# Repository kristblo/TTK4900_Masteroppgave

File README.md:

# TTK4900 Masteroppgave

Welcome to the Git repo of the master thesis project of Kristian Blom the spring of 2024, in which a defunct robotic arm from the 1990s was refurbished with new control hardware and software.

The main branch presents the project as it was at the end of the project's implementation, and shall not be altered until final censure has fallen on the project report.

The censure branch presents a curated version of project items deemed relevant to censure. Should the censor(s) find the main branch unnecessarily cluttered, this branch may be of interest.

### Directory: PCBs
Contains KiCad PCB design files.

### Directory: code/ros
Contains all code pertaining to ROS nodes and their configuration.

### Directory: code/stm config official
Contains all code pertaining to arm onboard software modules.

### Directory: documentation external
Contains hardware datasheets, application notes etc. for units used in the project. Most of these are cited as sources in the report.

### Directory: documentation internal
Contains documentation generated for the project.

The file journal.md contains notes taken during development.

A PDF version of the generated code documentation may be found here, in the file "kristian\_blom\_ttk4900\_documentation.pdf".

An HTML version of the generated code documentation may be found here, in the file "kristian\_blom\_ttk4900\_documentation\_html.zip". Its contents may be accessed by downloading and extracting the zip, then accessing "index.html" from a web browser.

Should the configuration of the STM32F303 processor be of interest, beyond what is presented in the thesis, an automatically generated report may be found in "stm\_config\_official.pdf"

Other items in this directory deemed relevant to the censure of the project are presented in the thesis, and may safely be ignored.

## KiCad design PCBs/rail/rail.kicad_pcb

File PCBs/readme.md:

###Folder purpose: PCB designs with Mk1.1 updates implemented, as well as production files such as gerbers

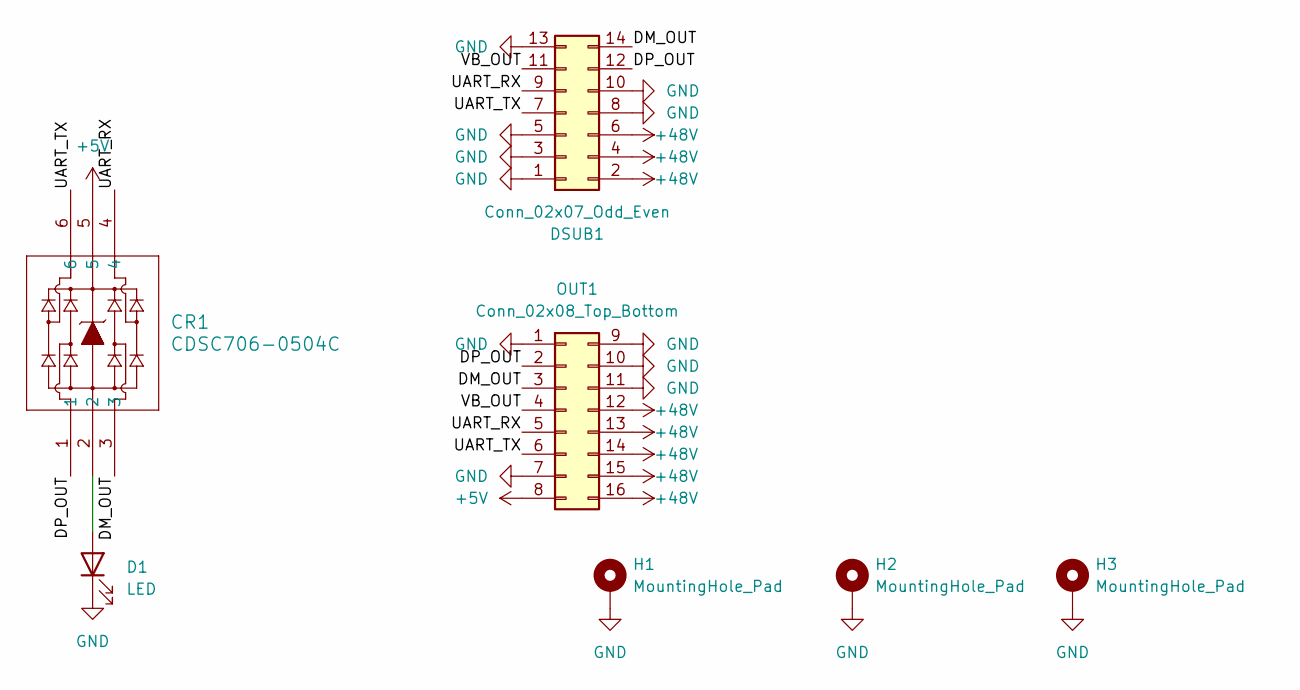
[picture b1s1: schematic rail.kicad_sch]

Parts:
CR1: CDSC706-0504C; CDSC706-0504C_BRN
D1: LED; LED_0603_1608Metric
DSUB1: Conn_02x07_Odd_Even; PinHeader_2x07_P2.54mm_Vertical
H1, H2, H3: MountingHole_Pad; MountingHole_3.2mm_M3_DIN965_Pad_TopBottom
OUT1: Conn_02x08_Top_Bottom; 2-1761603-6_TYC

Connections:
+5V: CR1.5, OUT1.8
+48V: DSUB1.2, DSUB1.4, DSUB1.6, OUT1.12, OUT1.13, OUT1.14, OUT1.15, OUT1.16
/DM_OUT: CR1.3, DSUB1.14, OUT1.3
/DP_OUT: CR1.1, DSUB1.12, OUT1.2
/UART_RX: CR1.4, DSUB1.9, OUT1.5
/UART_TX: CR1.6, DSUB1.7, OUT1.6
/VB_OUT: DSUB1.11, OUT1.4
GND: D1.1 (K), DSUB1.1, DSUB1.3, DSUB1.5, DSUB1.8, DSUB1.10, DSUB1.13, H1.1, H2.1, H3.1, OUT1.1, OUT1.7, OUT1.9, OUT1.10, OUT1.11
unnamed: CR1.2, D1.2 (A)

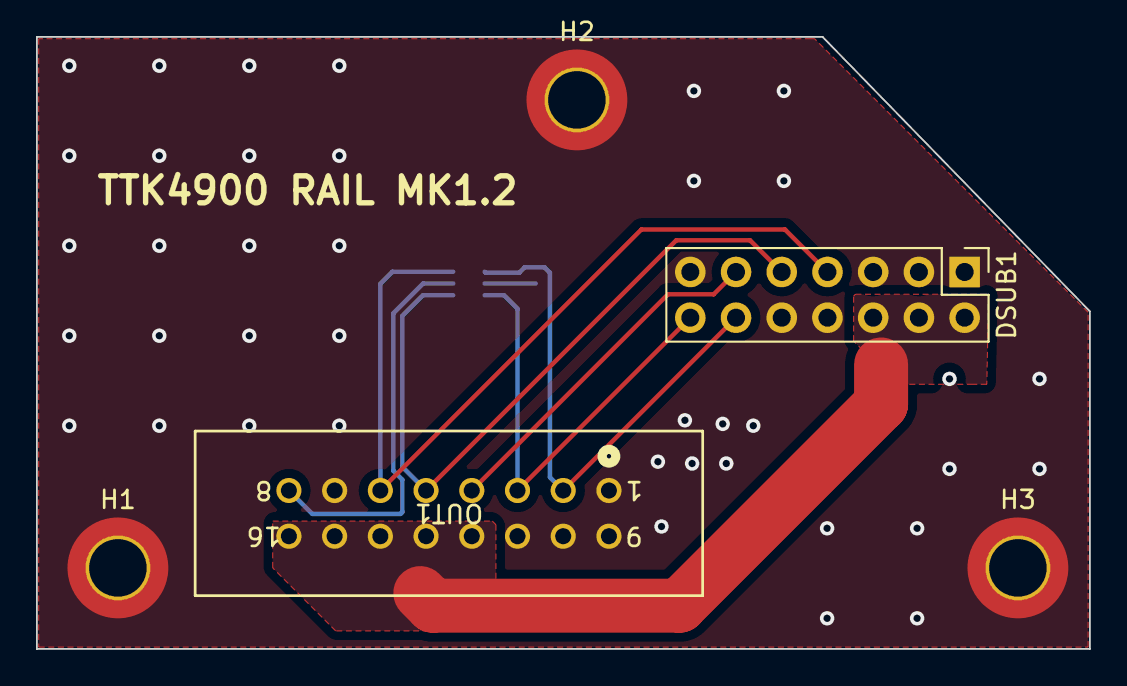
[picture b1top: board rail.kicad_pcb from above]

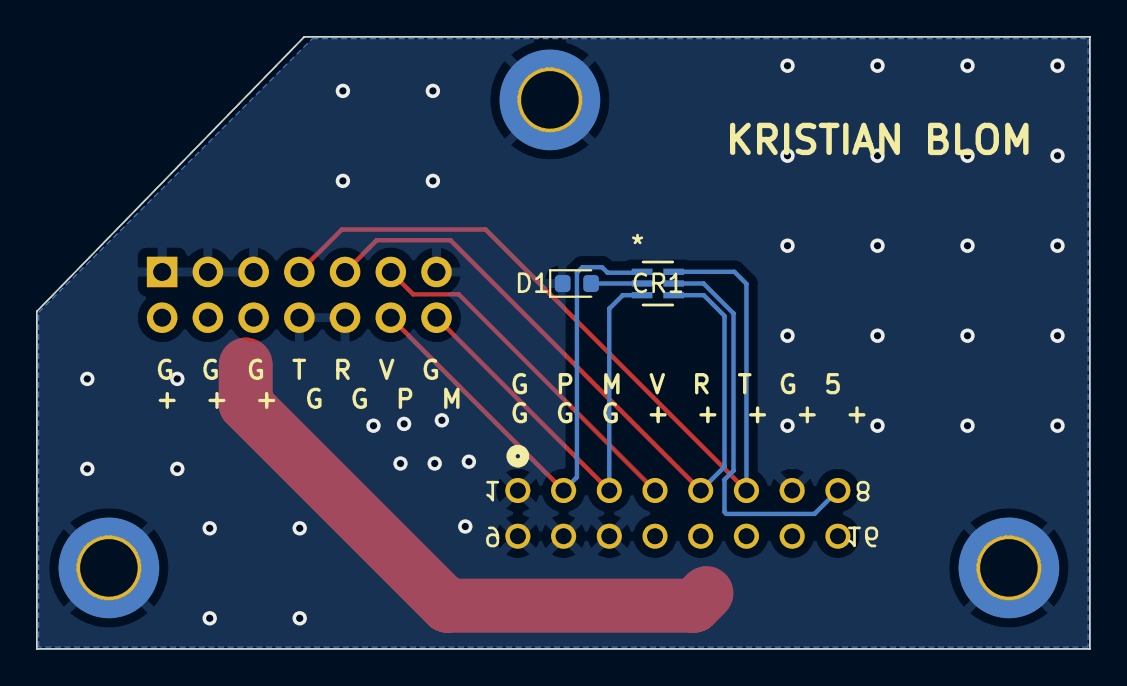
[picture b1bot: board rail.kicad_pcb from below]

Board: 2 copper layers, 58.5 x 34.0 mm, 7 parts (2 on the bottom side), 9 nets.

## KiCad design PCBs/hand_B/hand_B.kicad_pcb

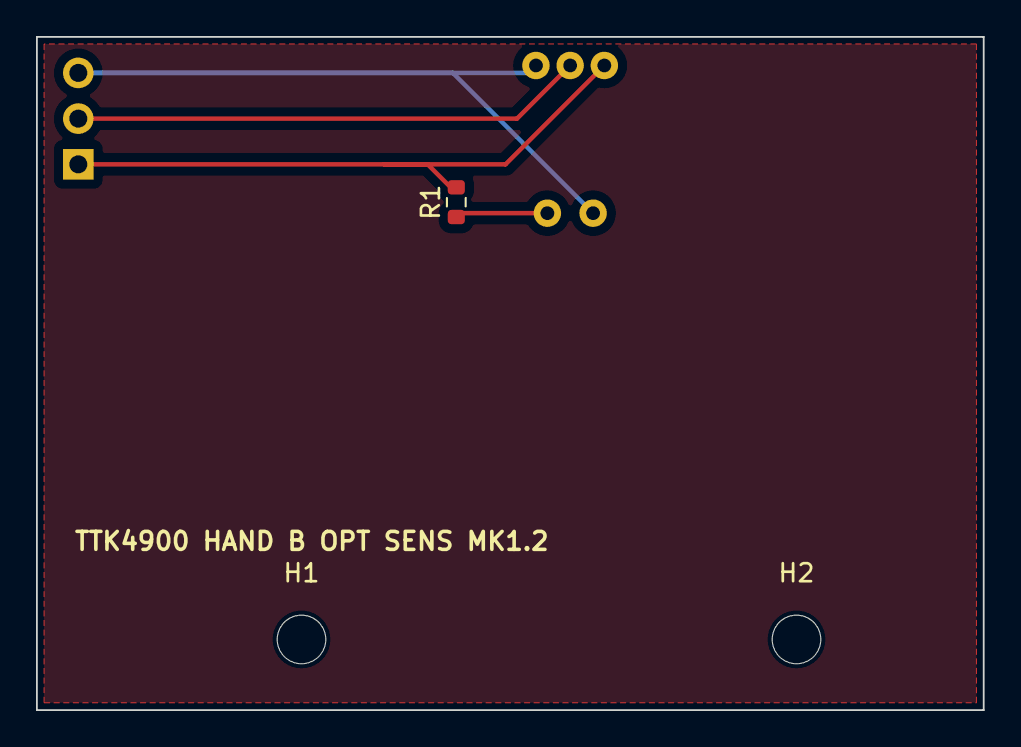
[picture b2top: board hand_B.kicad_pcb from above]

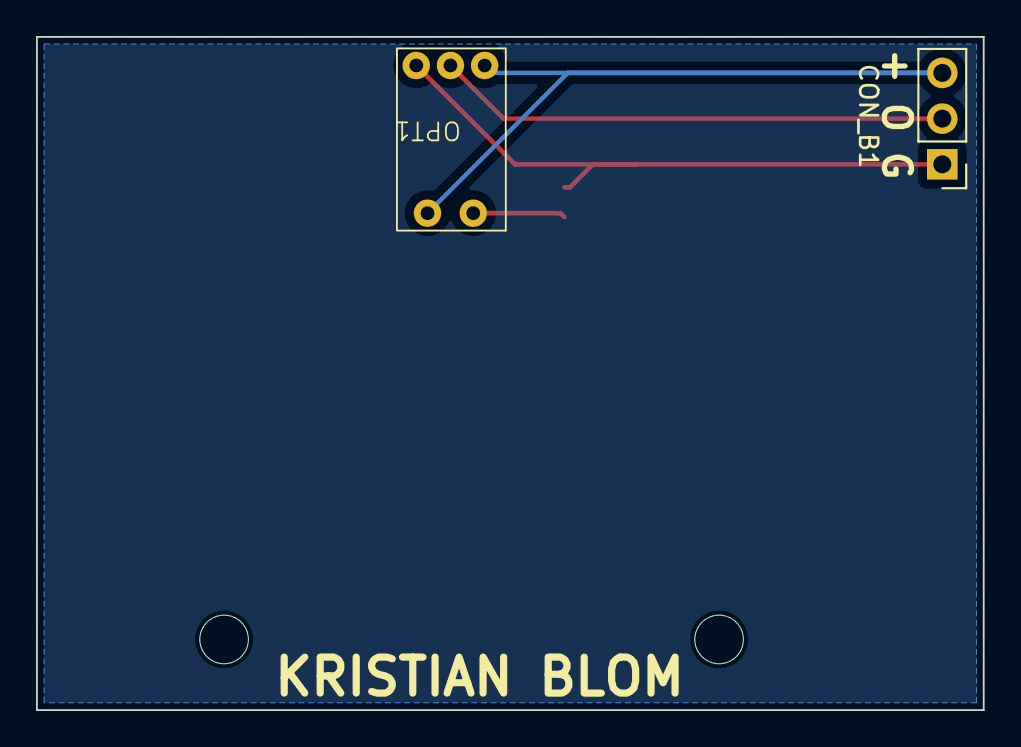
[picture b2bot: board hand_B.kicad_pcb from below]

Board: 2 copper layers, 52.6 x 37.4 mm, 5 parts (2 on the bottom side), 4 nets.

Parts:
CON_B1: Conn_01x03; PinHeader_1x03_P2.54mm_Vertical
H1, H2: MountingHole; MountingHole_2.7mm_M2.5
OPT1: OPB971N51
R1: 220; R_0603_1608Metric

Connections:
/0v: CON_B1.1, OPT1.5 (GND), R1.2
/5V: CON_B1.3, OPT1.1 (Anode), OPT1.3 (Vcc)
/OPT_B: CON_B1.2, OPT1.4 (Output)
unnamed: OPT1.2 (Cathode), R1.1

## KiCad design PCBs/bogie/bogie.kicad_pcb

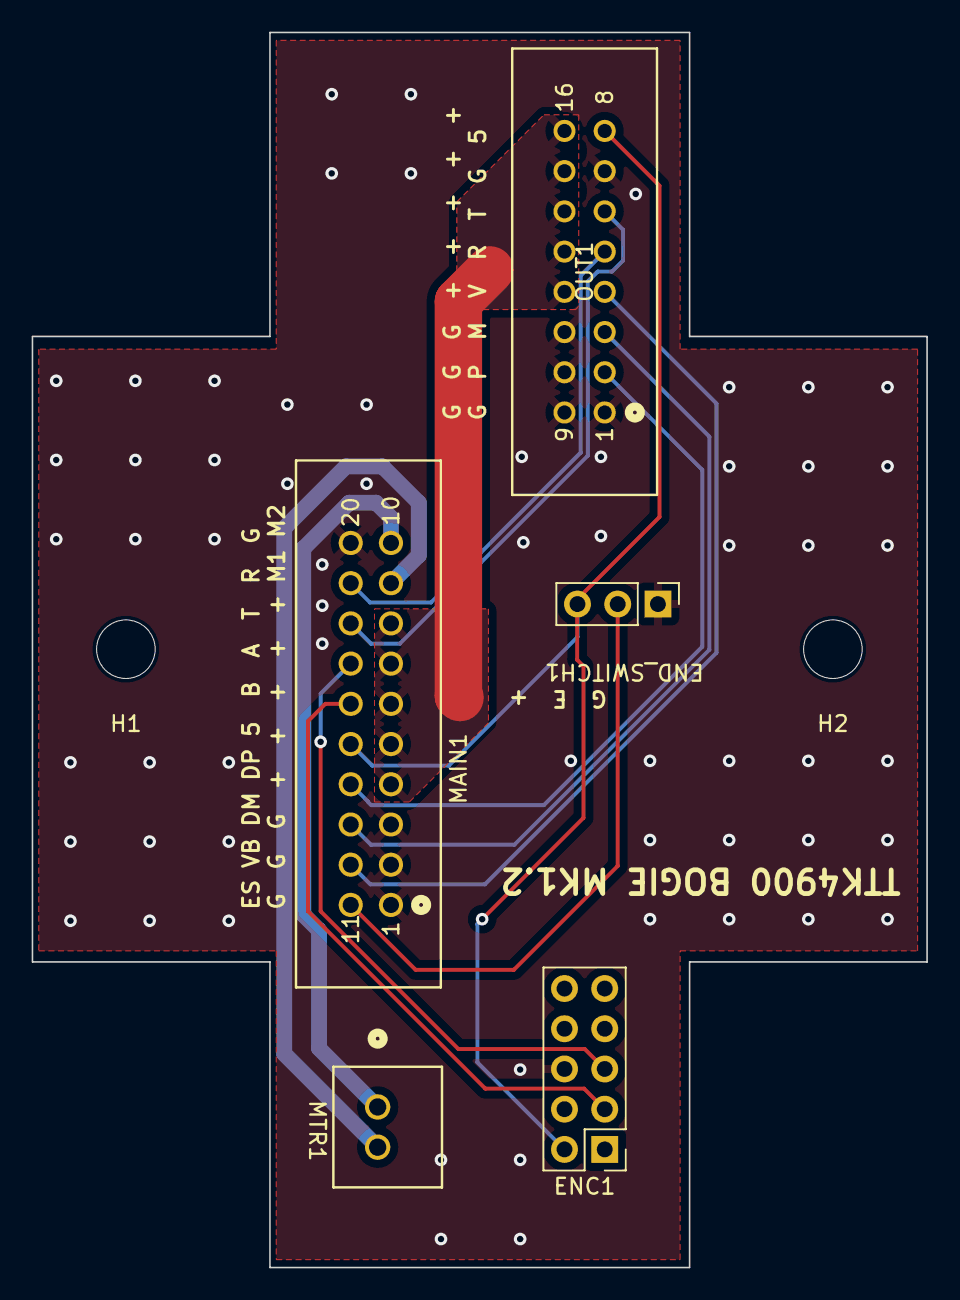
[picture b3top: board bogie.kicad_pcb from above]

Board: 2 copper layers, 56.5 x 78.0 mm, 7 parts (0 on the bottom side), 13 nets.

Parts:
ENC1: Conn_02x05_Odd_Even; PinHeader_2x05_P2.54mm_Vertical
END_SWITCH1: Conn_01x03; PinHeader_1x03_P2.54mm_Vertical
H1, H2: MountingHole; MountingHole_3.7mm
MAIN1: Conn_02x10_Top_Bottom; 1761681-7_TYC
MTR1: Conn_01x02; 70543-0001_MOL
OUT1: Conn_02x08_Top_Bottom; 2-1761603-6_TYC

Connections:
+5V: ENC1.2, END_SWITCH1.3, MAIN1.15, OUT1.8
+48V: MAIN1.4, MAIN1.5, MAIN1.6, MAIN1.7, MAIN1.8, OUT1.12, OUT1.13, OUT1.14, OUT1.15, OUT1.16
/DM_OUT: MAIN1.13, OUT1.3
/DP_OUT: MAIN1.14, OUT1.2
/ENC1A: ENC1.3, MAIN1.16
/ENC1B: ENC1.5, MAIN1.17
/END_SWITCH: END_SWITCH1.2, MAIN1.11
/MTR1_IN: MAIN1.10, MTR1.1
/MTR1_OUT: MAIN1.9, MTR1.2
/UART_RX: MAIN1.19, OUT1.5
/UART_TX: MAIN1.18, OUT1.6
/VB_OUT: MAIN1.12, OUT1.4
GND: ENC1.6, END_SWITCH1.1, MAIN1.1, MAIN1.2, MAIN1.3, MAIN1.20, OUT1.1, OUT1.7, OUT1.9, OUT1.10, OUT1.11

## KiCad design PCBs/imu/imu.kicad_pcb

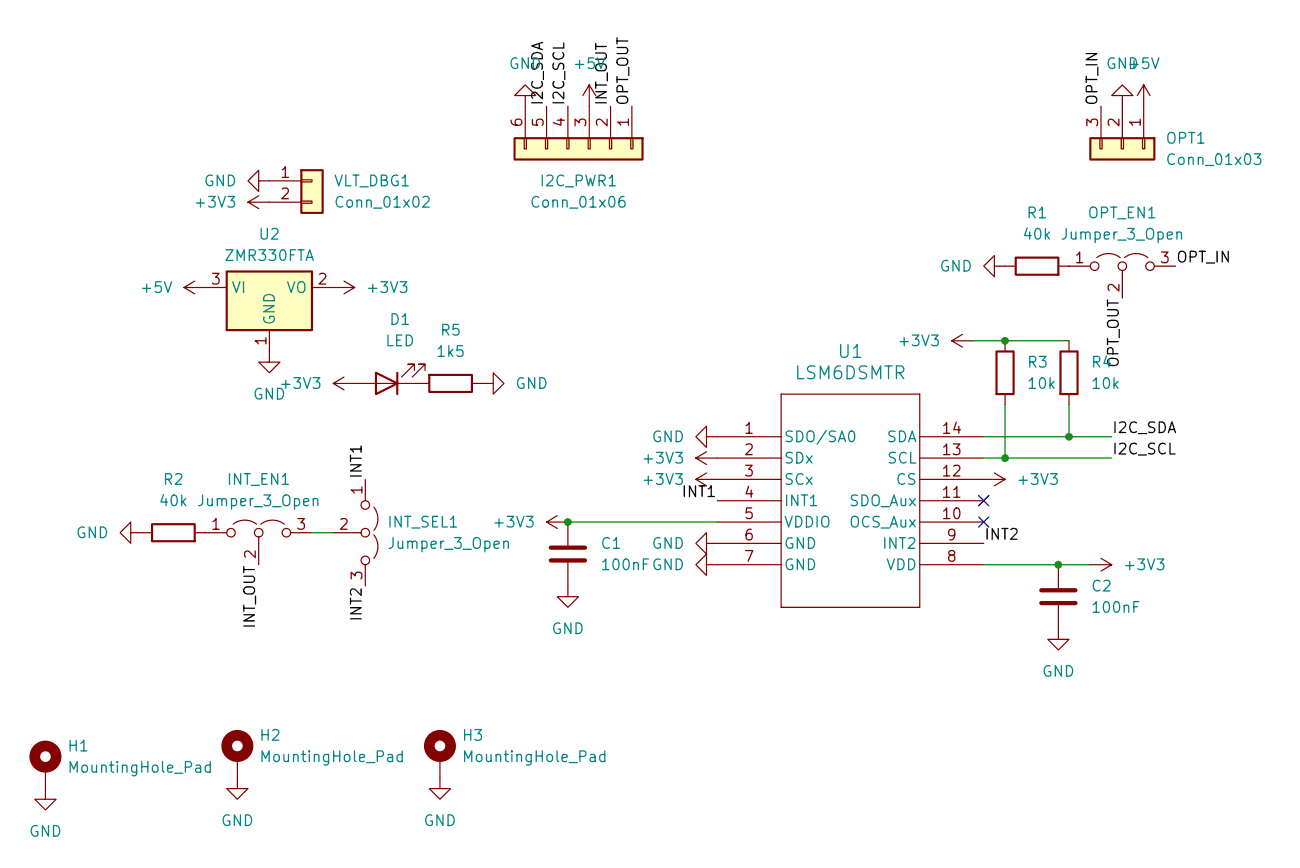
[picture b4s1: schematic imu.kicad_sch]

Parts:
C1, C2: 100nF; C_0603_1608Metric
D1: LED; LED_0603_1608Metric
H1, H2, H3: MountingHole_Pad; MountingHole_3.2mm_M3_DIN965_Pad_TopBottom
I2C_PWR1: Conn_01x06; PinHeader_1x06_P2.54mm_Vertical
INT_EN1: Jumper_3_Open; PinHeader_1x03_P2.54mm_Vertical
INT_SEL1: Jumper_3_Open; PinHeader_1x03_P2.54mm_Vertical
OPT1: Conn_01x03; PinHeader_1x03_P2.54mm_Vertical
OPT_EN1: Jumper_3_Open; PinHeader_1x03_P2.54mm_Vertical
R1, R2: 40k; R_0805_2012Metric
R3, R4: 10k; R_0805_2012Metric
R5: 1k5; R_0805_2012Metric
U1: LSM6DSMTR; LGA-14L_2P5X3X0P83_STM
U2: ZMR330FTA; SOT-23-3
VLT_DBG1: Conn_01x02; PinHeader_1x02_P2.54mm_Vertical

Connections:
+3V3: C1.2, C2.2, D1.2 (A), R3.1, R4.1, U1.2 (SDx), U1.3 (SCx), U1.5 (VDDIO), U1.8 (VDD), U1.12 (CS), U2.2 (VO), VLT_DBG1.2
+5V: I2C_PWR1.3, OPT1.1, U2.3 (VI)
/I2C_SCL: I2C_PWR1.4, R3.2, U1.13 (SCL)
/I2C_SDA: I2C_PWR1.5, R4.2, U1.14 (SDA)
/INT1: INT_SEL1.1 (A), U1.4 (INT1)
/INT2: INT_SEL1.3 (B), U1.9 (INT2)
/INT_OUT: I2C_PWR1.2, INT_EN1.2 (C)
/OPT_IN: OPT1.3, OPT_EN1.3 (B)
/OPT_OUT: I2C_PWR1.1, OPT_EN1.2 (C)
GND: C1.1, C2.1, H1.1, H2.1, H3.1, I2C_PWR1.6, OPT1.2, R1.1, R2.1, R5.1, U1.1 (SDO/SA0), U1.6 (GND), U1.7 (GND), U2.1 (GND), VLT_DBG1.1
unnamed: D1.1 (K), R5.2
unnamed: INT_EN1.1 (A), R2.2
unnamed: INT_EN1.3 (B), INT_SEL1.2 (C)
unnamed: OPT_EN1.1 (A), R1.2

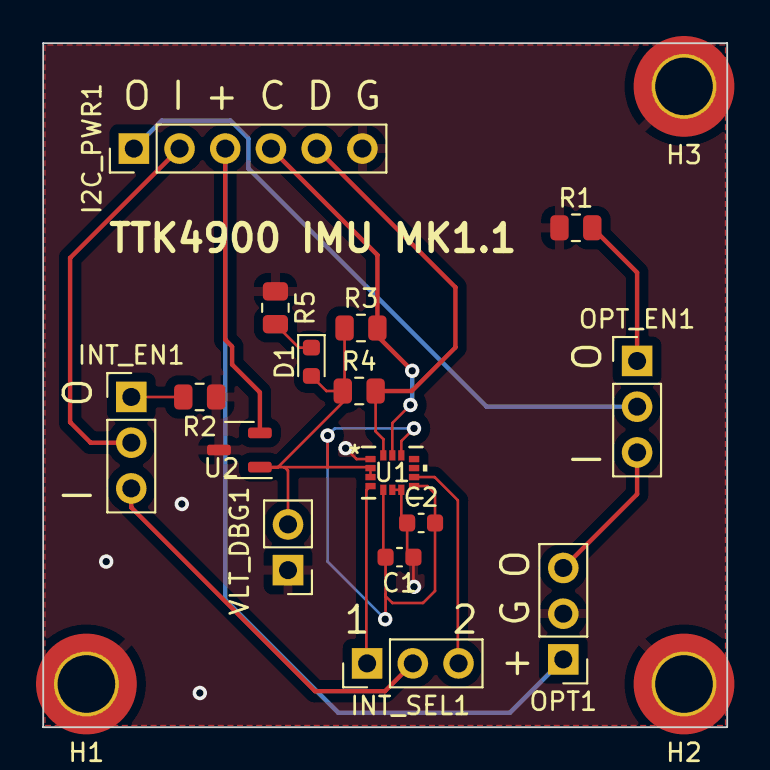
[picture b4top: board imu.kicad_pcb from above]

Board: 2 copper layers, 38.0 x 38.0 mm, 19 parts (0 on the bottom side), 14 nets.

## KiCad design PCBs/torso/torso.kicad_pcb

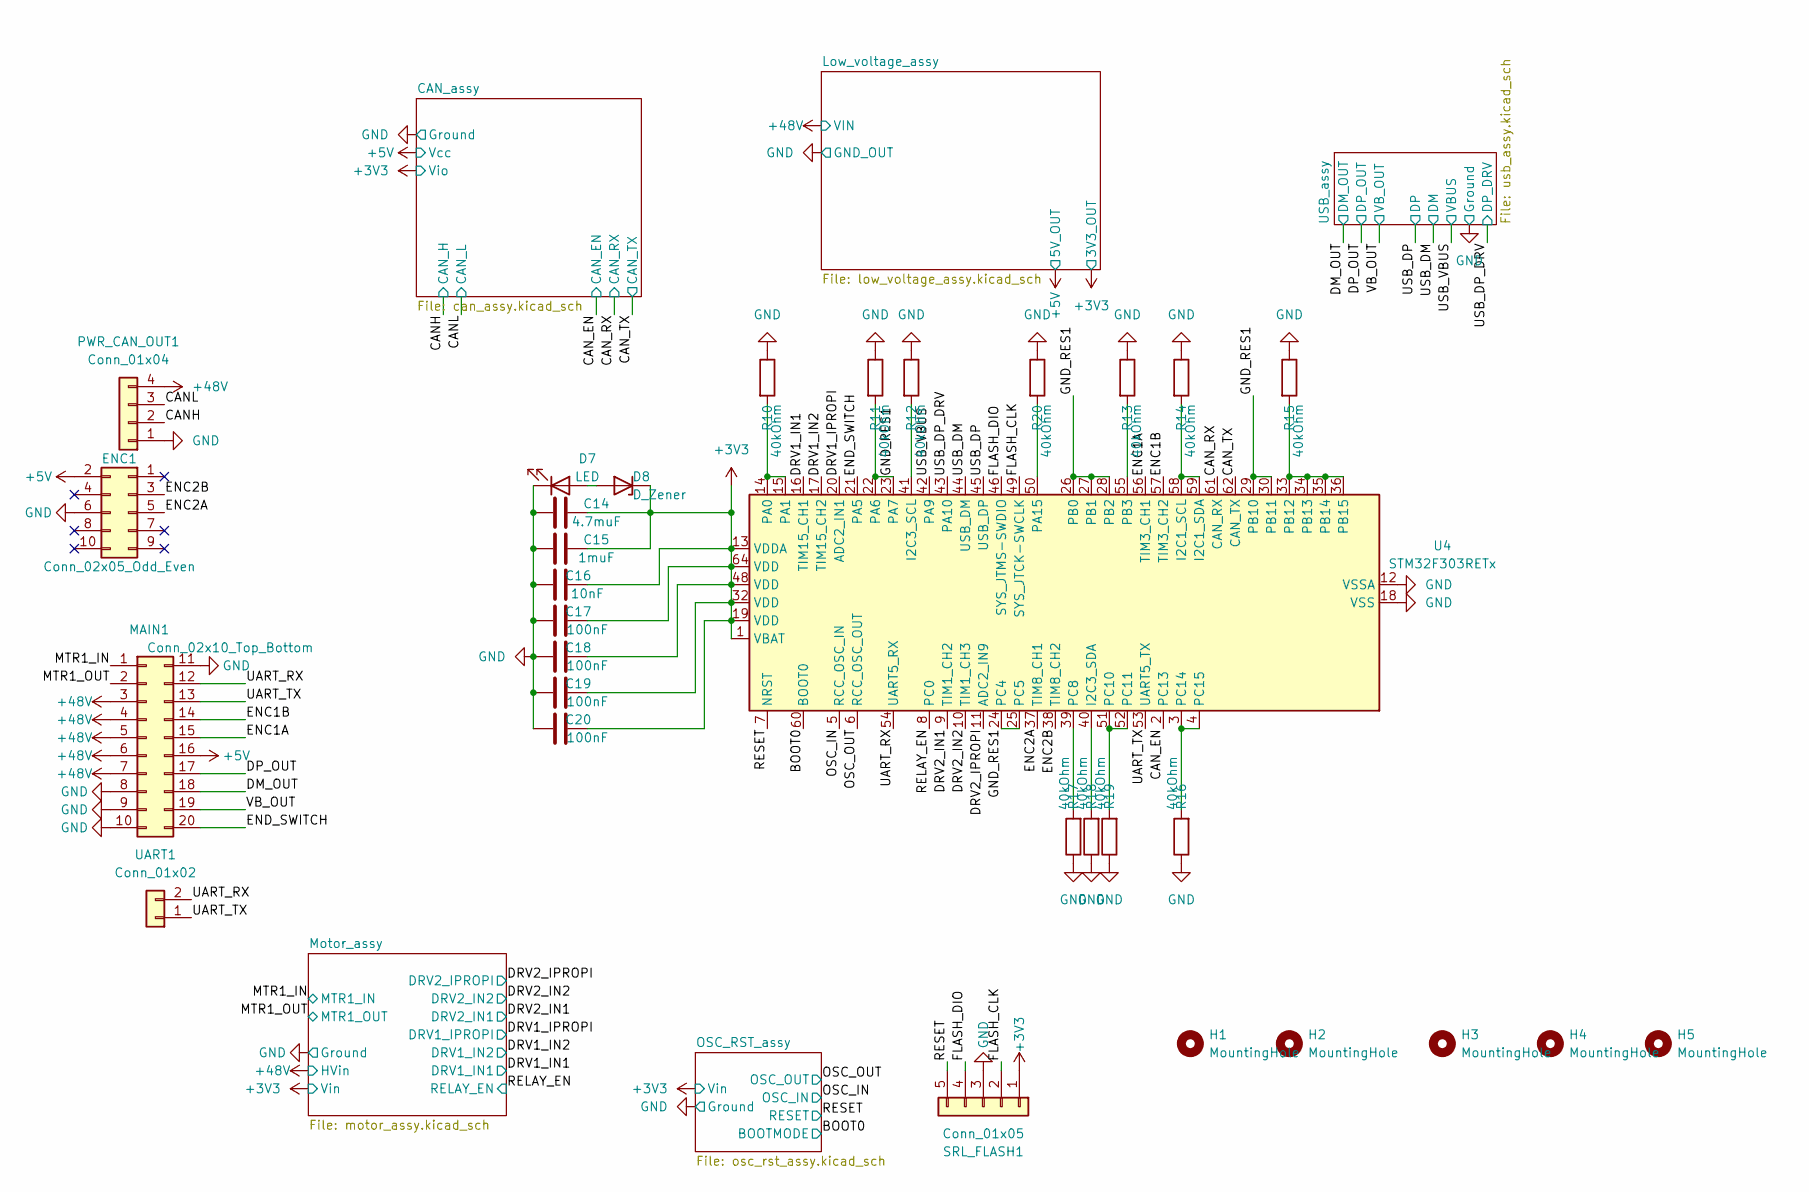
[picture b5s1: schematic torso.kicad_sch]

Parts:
C14: 4.7muF; C_0603_1608Metric
C15: 1muF; C_0603_1608Metric
C16: 10nF; C_0603_1608Metric
C17, C18, C19, C20: 100nF; C_0603_1608Metric
D7: LED; LED_0603_1608Metric
D8: D_Zener; D_T-1_P5.08mm_Horizontal
ENC1: Conn_02x05_Odd_Even; PinHeader_2x05_P2.54mm_Vertical
H1, H2: MountingHole; MountingHole_3.5mm
H3, H4, H5: MountingHole; MountingHole_5.3mm_M5
MAIN1: Conn_02x10_Top_Bottom; 1761681-7_TYC
PWR_CAN_OUT1: Conn_01x04; TerminalBlock_4Ucon_1x04_P3.50mm_Vertical
R10, R11, R12, R13, R14, R15, R16, R17, R18, R19, R20: 40kOhm; R_0402_1005Metric
SRL_FLASH1: Conn_01x05; PinHeader_1x05_P2.54mm_Vertical
U4: STM32F303RETx; LQFP-64_10x10mm_P0.5mm
UART1: Conn_01x02; PinHeader_1x02_P2.54mm_Vertical

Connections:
+3V3: C14.1, C15.1, C16.2, C17.2, C18.2, C19.2, C20.2, D8.1 (K), SRL_FLASH1.1, U4.1 (VBAT), U4.13 (VDDA), U4.19 (VDD), U4.32 (VDD), U4.48 (VDD), U4.64 (VDD); also elsewhere on the board
+5V: ENC1.2, MAIN1.16; also elsewhere on the board
+48V: MAIN1.3, MAIN1.4, MAIN1.5, MAIN1.6, MAIN1.7, PWR_CAN_OUT1.4 (48V); also elsewhere on the board
/BOOT0: U4.60 (BOOT0); also elsewhere on the board
/CANH: PWR_CAN_OUT1.2 (CANH); also elsewhere on the board
/CANL: PWR_CAN_OUT1.3 (CANL); also elsewhere on the board
/CAN_EN: U4.2 (PC13); also elsewhere on the board
/CAN_RX: U4.61 (CAN_RX); also elsewhere on the board
/CAN_TX: U4.62 (CAN_TX); also elsewhere on the board
/DM_OUT: MAIN1.18; also elsewhere on the board
/DP_OUT: MAIN1.17; also elsewhere on the board
/DRV1_IN1: U4.16 (TIM15_CH1); also elsewhere on the board
/DRV1_IN2: U4.17 (TIM15_CH2); also elsewhere on the board
/DRV1_IPROPI: U4.20 (ADC2_IN1); also elsewhere on the board
/DRV2_IN1: U4.9 (TIM1_CH2); also elsewhere on the board
/DRV2_IN2: U4.10 (TIM1_CH3); also elsewhere on the board
/DRV2_IPROPI: U4.11 (ADC2_IN9); also elsewhere on the board
/ENC1A: MAIN1.15, U4.56 (TIM3_CH1)
/ENC1B: MAIN1.14, U4.57 (TIM3_CH2)
/ENC2A: ENC1.5, U4.37 (TIM8_CH1)
/ENC2B: ENC1.3, U4.38 (TIM8_CH2)
/END_SWITCH: MAIN1.20, U4.21 (PA5)
/FLASH_CLK: SRL_FLASH1.2, U4.49 (SYS_JTCK-SWCLK)
/FLASH_DIO: SRL_FLASH1.4, U4.46 (SYS_JTMS-SWDIO)
/GND_RES1: R11.2, U4.22 (PA6), U4.23 (PA7), U4.24 (PC4), U4.25 (PC5), U4.26 (PB0), U4.27 (PB1), U4.28 (PB2), U4.29 (PB10), U4.30 (PB11)
/MTR1_IN: MAIN1.1; also elsewhere on the board
/MTR1_OUT: MAIN1.2; also elsewhere on the board
/OSC_IN: U4.5 (RCC_OSC_IN); also elsewhere on the board
/OSC_OUT: U4.6 (RCC_OSC_OUT); also elsewhere on the board
/RELAY_EN: U4.8 (PC0); also elsewhere on the board
/RESET: SRL_FLASH1.5, U4.7 (NRST); also elsewhere on the board
/UART_RX: MAIN1.12, U4.54 (UART5_RX), UART1.2
/UART_TX: MAIN1.13, U4.53 (UART5_TX), UART1.1
/USB_DM: U4.44 (USB_DM); also elsewhere on the board
/USB_DP: U4.45 (USB_DP); also elsewhere on the board
/USB_DP_DRV: U4.43 (PA10); also elsewhere on the board
/USB_VBUS: U4.42 (PA9); also elsewhere on the board
/VB_OUT: MAIN1.19; also elsewhere on the board
GND: C14.2, C15.2, C16.1, C17.1, C18.1, C19.1, C20.1, D7.1 (K), ENC1.6, MAIN1.8, MAIN1.9, MAIN1.10, MAIN1.11, PWR_CAN_OUT1.1 (GND), R10.1, R11.1, R12.1, R13.1, R14.1, R15.1, R16.1, R17.1, R18.1, R19.1, R20.1, SRL_FLASH1.3, U4.12 (VSSA), U4.18 (VSS), U4.31 (VSS), U4.47 (VSS), U4.63 (VSS); also elsewhere on the board
unnamed: D7.2 (A), D8.2 (A)
unnamed: R10.2, U4.14 (PA0), U4.15 (PA1)
unnamed: R12.2, U4.41 (I2C3_SCL)
unnamed: R20.2, U4.50 (PA15)
unnamed: R13.2, U4.55 (PB3)
unnamed: R14.2, U4.58 (I2C1_SCL), U4.59 (I2C1_SDA)
unnamed: R15.2, U4.33 (PB12), U4.34 (PB13), U4.35 (PB14), U4.36 (PB15)
unnamed: R17.2, U4.39 (PC8)
unnamed: R18.2, U4.40 (I2C3_SDA)
unnamed: R19.2, U4.51 (PC10), U4.52 (PC11)
unnamed: R16.2, U4.3 (PC14), U4.4 (PC15)

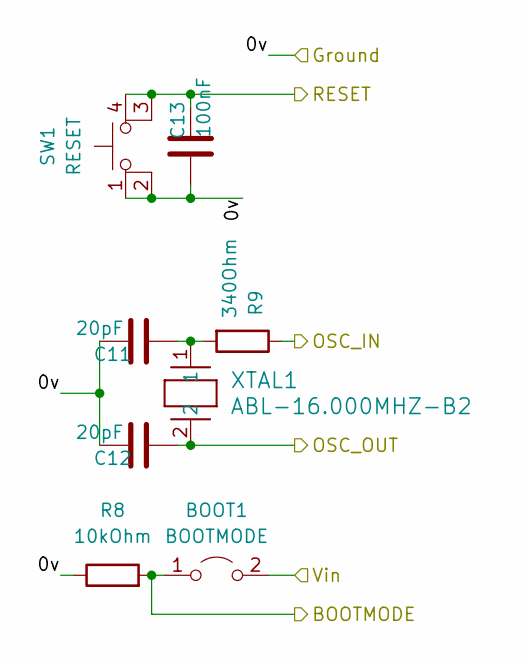
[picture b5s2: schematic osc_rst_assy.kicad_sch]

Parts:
BOOT1: BOOTMODE; PinHeader_1x02_P2.54mm_Vertical
C11, C12: 20pF; C_0603_1608Metric
C13: 100nF; C_0603_1608Metric
R8: 10kOhm; R_0805_2012Metric
R9: 340Ohm; R_0805_2012Metric
SW1: RESET; SW_Push_1P1T_NO_CK_KSC6xxJ
XTAL1: ABL-16.000MHZ-B2; XTAL_ABL-16_ABR

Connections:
+3V3: BOOT1.2 (B); also elsewhere on the board
/BOOT0: BOOT1.1 (A), R8.2; also elsewhere on the board
/OSC_IN: R9.1; also elsewhere on the board
/OSC_OUT: C12.1, XTAL1.2; also elsewhere on the board
/RESET: C13.2, SW1.3 (K), SW1.4 (A); also elsewhere on the board
GND: C11.2, C12.2, C13.1, R8.1, SW1.1, SW1.2; also elsewhere on the board
unnamed: C11.1, R9.2, XTAL1.1

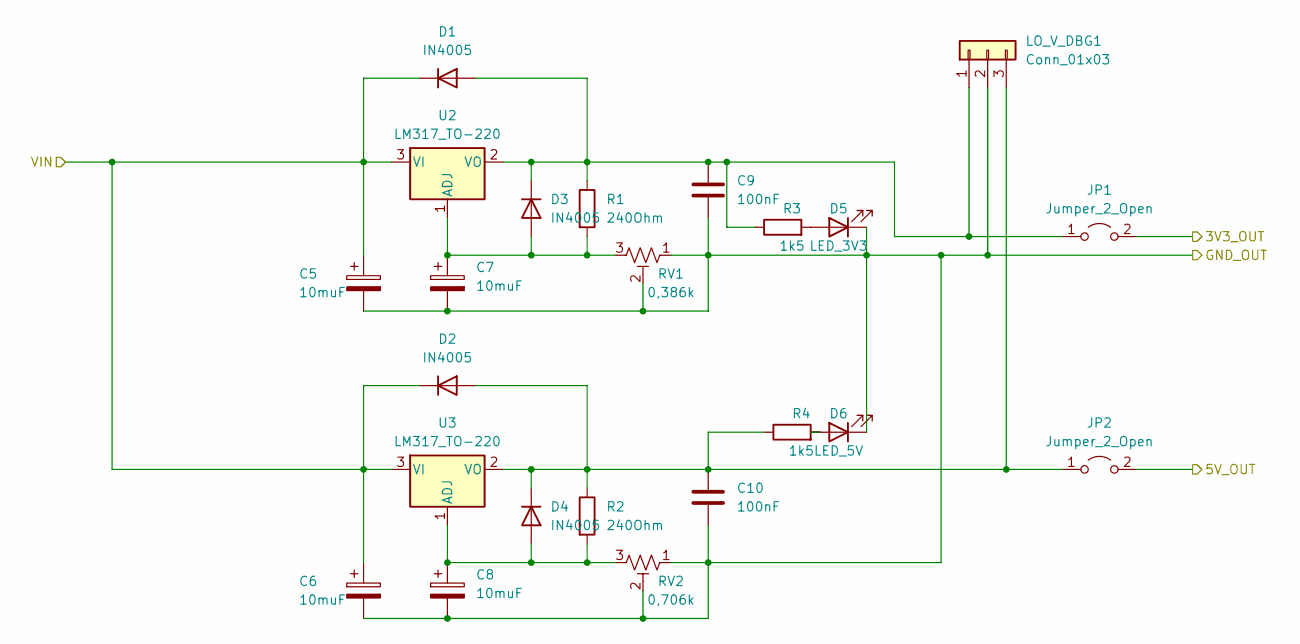
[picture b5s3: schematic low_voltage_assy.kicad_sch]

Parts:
C5, C6, C7, C8: 10muF; CP_Radial_D5.0mm_P2.00mm
C9, C10: 100nF; C_0603_1608Metric
D1, D2, D3, D4: IN4005; D_T-1_P5.08mm_Horizontal
D5: LED_3V3; LED_0603_1608Metric
D6: LED_5V; LED_0603_1608Metric
JP1, JP2: Jumper_2_Open; PinHeader_1x02_P2.54mm_Vertical
LO_V_DBG1: Conn_01x03; PinHeader_1x03_P2.54mm_Vertical
R1, R2: 240Ohm; R_0805_2012Metric
R3, R4: 1k5; R_0805_2012Metric
RV1: 0,386k; Potentiometer_Bourns_3006P_Horizontal
RV2: 0,706k; Potentiometer_Bourns_3006P_Horizontal
U2, U3: LM317_TO-220; TO-220-3_Horizontal_TabDown

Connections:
+3V3: JP1.2 (B); also elsewhere on the board
+5V: JP2.2 (B); also elsewhere on the board
+48V: C5.1, C6.1, D1.1 (K), D2.1 (K), U2.3 (VI), U3.3 (VI); also elsewhere on the board
GND: C5.2, C6.2, C7.2, C8.2, C9.2, C10.2, D5.1 (K), D6.1 (K), LO_V_DBG1.2, RV1.1, RV1.2, RV2.1, RV2.2; also elsewhere on the board
unnamed: C9.1, D1.2 (A), D3.1 (K), JP1.1 (A), LO_V_DBG1.1, R1.1, R3.1, U2.2 (VO)
unnamed: C10.1, D2.2 (A), D4.1 (K), JP2.1 (A), LO_V_DBG1.3, R2.1, R4.1, U3.2 (VO)
unnamed: C7.1, D3.2 (A), R1.2, RV1.3, U2.1 (ADJ)
unnamed: C8.1, D4.2 (A), R2.2, RV2.3, U3.1 (ADJ)
unnamed: D5.2 (A), R3.2
unnamed: D6.2 (A), R4.2

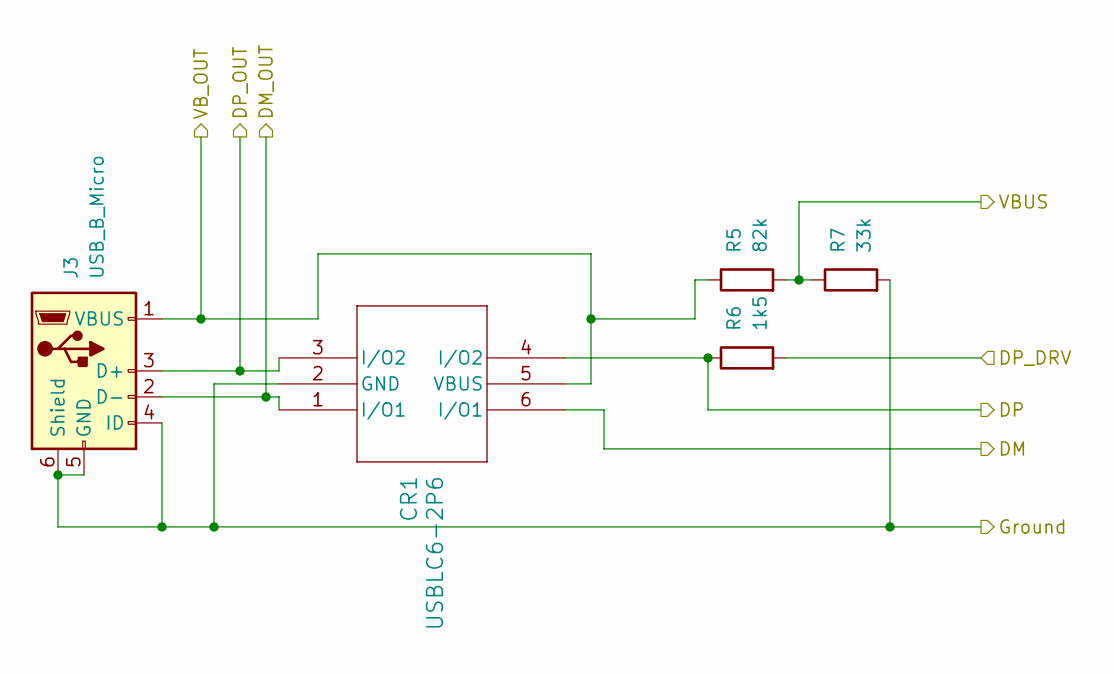
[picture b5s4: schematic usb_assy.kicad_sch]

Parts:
CR1: USBLC6-2P6; SOT-666_STM
J3: USB_B_Micro; USB_Micro-B_Molex-105017-0001
R5: 82k; R_0603_1608Metric_Pad0.98x0.95mm_HandSolder
R6: 1k5; R_0603_1608Metric_Pad0.98x0.95mm_HandSolder
R7: 33k; R_0603_1608Metric_Pad0.98x0.95mm_HandSolder

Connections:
/DM_OUT: CR1.1 (I/O1), J3.2 (D-); also elsewhere on the board
/DP_OUT: CR1.3 (I/O2), J3.3 (D+); also elsewhere on the board
/USB_DM: CR1.6 (I/O1); also elsewhere on the board
/USB_DP: CR1.4 (I/O2), R6.1; also elsewhere on the board
/USB_DP_DRV: R6.2; also elsewhere on the board
/USB_VBUS: R5.2, R7.1; also elsewhere on the board
/VB_OUT: CR1.5 (VBUS), J3.1 (VBUS), R5.1; also elsewhere on the board
GND: CR1.2 (GND), J3.4 (ID), J3.5 (GND), J3.6 (Shield), R7.2; also elsewhere on the board

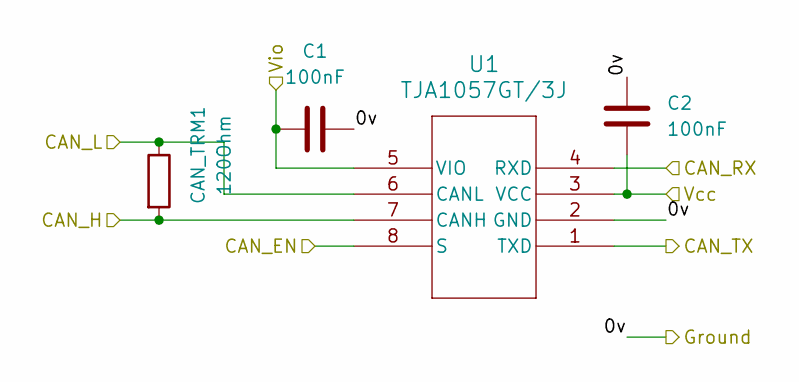
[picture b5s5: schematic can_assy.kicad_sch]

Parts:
C1, C2: 100nF; C_0603_1608Metric
CAN_TRM1: 120Ohm; R_0603_1608Metric
U1: TJA1057GT/3J; SOT96-1_SO8_NXP

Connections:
+3V3: C1.1, U1.5 (VIO); also elsewhere on the board
+5V: C2.1, U1.3 (VCC); also elsewhere on the board
/CANH: CAN_TRM1.2, U1.7 (CANH); also elsewhere on the board
/CANL: CAN_TRM1.1, U1.6 (CANL); also elsewhere on the board
/CAN_EN: U1.8 (S); also elsewhere on the board
/CAN_RX: U1.4 (RXD); also elsewhere on the board
/CAN_TX: U1.1 (TXD); also elsewhere on the board
GND: C1.2, C2.2, U1.2 (GND); also elsewhere on the board

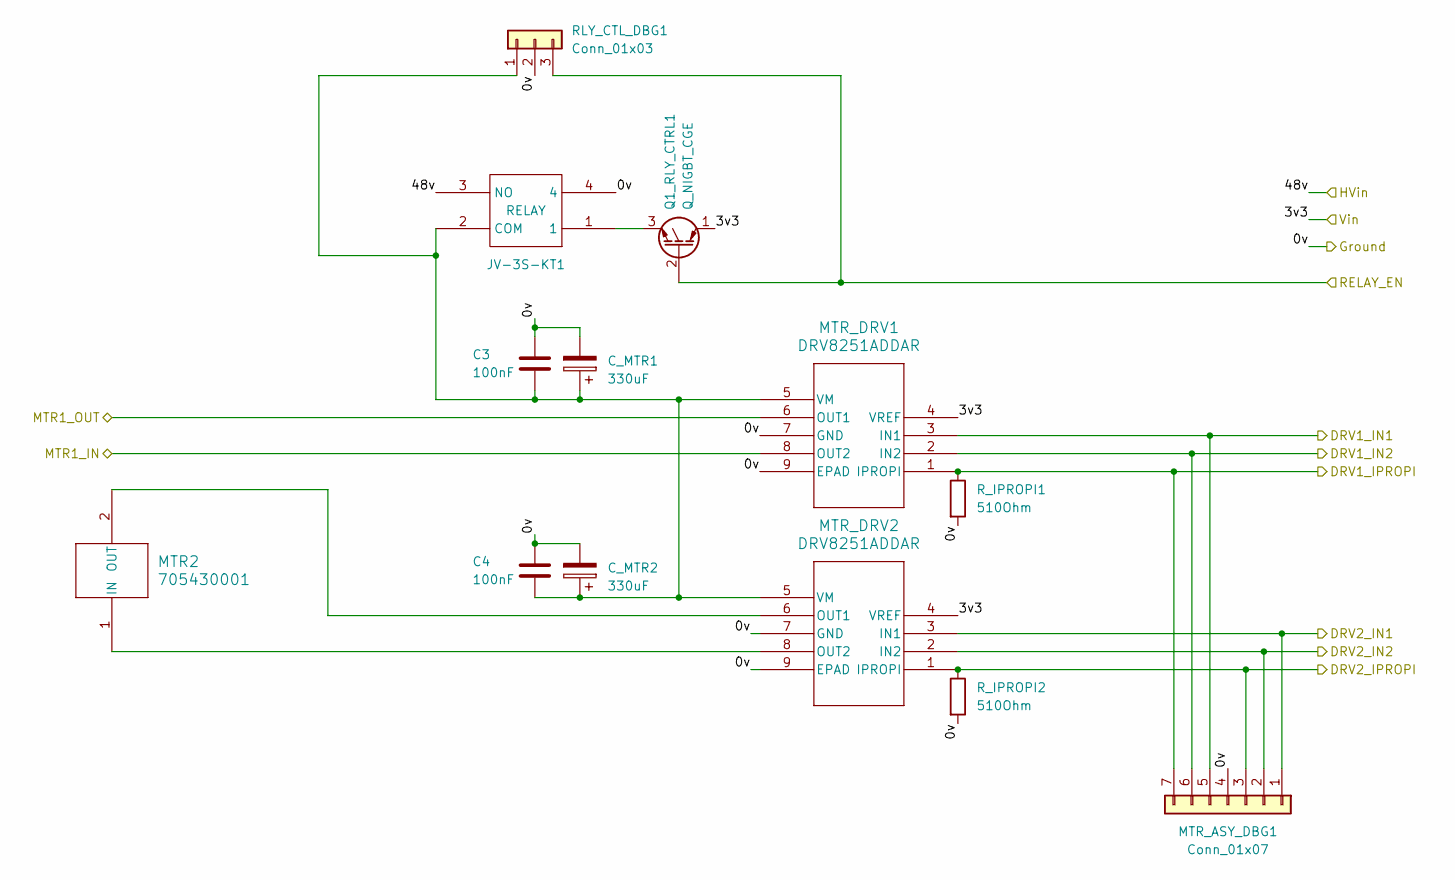
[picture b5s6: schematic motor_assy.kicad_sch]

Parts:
C3, C4: 100nF; C_0603_1608Metric
C_MTR1, C_MTR2: 330uF; CP_Radial_D16.0mm_P7.50mm
JV-3S-KT1: RELAY; JV-3S-KT
MTR2: 705430001; 70543-0001_MOL
MTR_ASY_DBG1: Conn_01x07; PinHeader_1x07_P2.54mm_Vertical
MTR_DRV1, MTR_DRV2: DRV8251ADDAR; SOIC8_DDA_TEX
Q1_RLY_CTRL1: Q_NIGBT_CGE; TO-92
RLY_CTL_DBG1: Conn_01x03; PinHeader_1x03_P2.54mm_Vertical
R_IPROPI1, R_IPROPI2: 510Ohm; R_0805_2012Metric

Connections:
+3V3: MTR_DRV1.4 (VREF), MTR_DRV2.4 (VREF), Q1_RLY_CTRL1.1 (C); also elsewhere on the board
+48V: JV-3S-KT1.3 (NO); also elsewhere on the board
/DRV1_IN1: MTR_ASY_DBG1.5, MTR_DRV1.3 (IN1); also elsewhere on the board
/DRV1_IN2: MTR_ASY_DBG1.6, MTR_DRV1.2 (IN2); also elsewhere on the board
/DRV1_IPROPI: MTR_ASY_DBG1.7, MTR_DRV1.1 (IPROPI), R_IPROPI1.1; also elsewhere on the board
/DRV2_IN1: MTR_ASY_DBG1.1, MTR_DRV2.3 (IN1); also elsewhere on the board
/DRV2_IN2: MTR_ASY_DBG1.2, MTR_DRV2.2 (IN2); also elsewhere on the board
/DRV2_IPROPI: MTR_ASY_DBG1.3, MTR_DRV2.1 (IPROPI), R_IPROPI2.1; also elsewhere on the board
/MTR1_IN: MTR_DRV1.8 (OUT2); also elsewhere on the board
/MTR1_OUT: MTR_DRV1.6 (OUT1); also elsewhere on the board
/RELAY_EN: Q1_RLY_CTRL1.2 (G), RLY_CTL_DBG1.3; also elsewhere on the board
GND: C3.1, C4.1, C_MTR1.2, C_MTR2.2, JV-3S-KT1.4, MTR_ASY_DBG1.4, MTR_DRV1.7 (GND), MTR_DRV1.9 (EPAD), MTR_DRV2.7 (GND), MTR_DRV2.9 (EPAD), RLY_CTL_DBG1.2, R_IPROPI1.2, R_IPROPI2.2; also elsewhere on the board
unnamed: C3.2, C4.2, C_MTR1.1, C_MTR2.1, JV-3S-KT1.2 (COM), MTR_DRV1.5 (VM), MTR_DRV2.5 (VM), RLY_CTL_DBG1.1
unnamed: MTR2.1 (IN), MTR_DRV2.8 (OUT2)
unnamed: MTR2.2 (OUT), MTR_DRV2.6 (OUT1)
unnamed: JV-3S-KT1.1, Q1_RLY_CTRL1.3 (E)

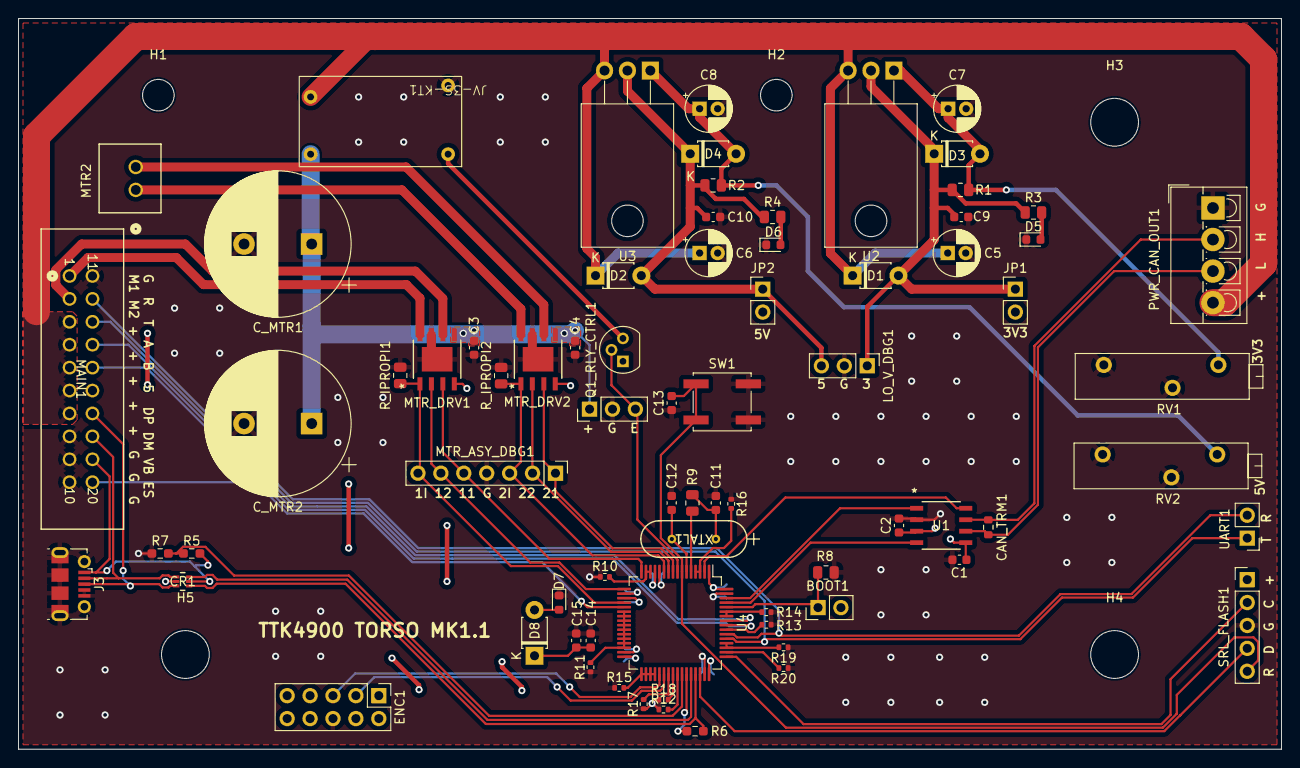
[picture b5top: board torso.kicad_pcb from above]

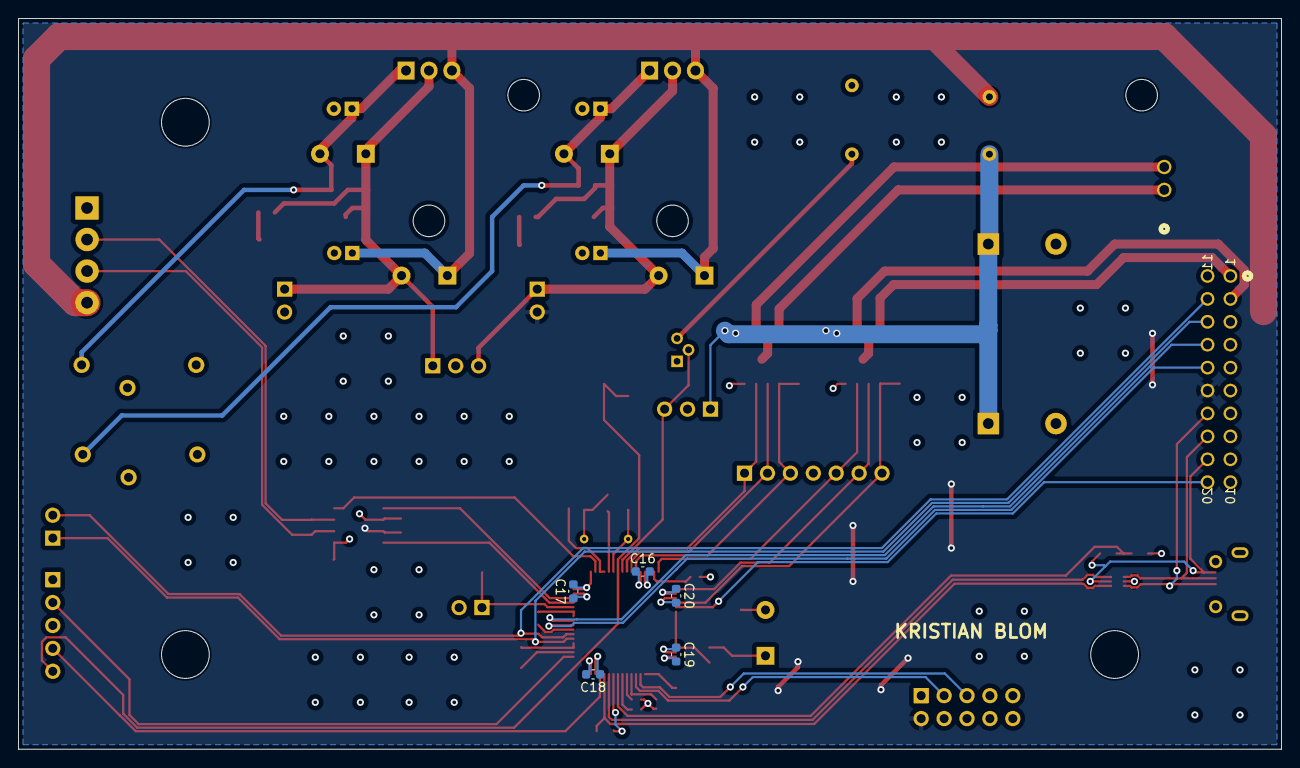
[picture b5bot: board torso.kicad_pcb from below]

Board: 4 copper layers, 140.0 x 81.0 mm, 84 parts (5 on the bottom side), 61 nets.
